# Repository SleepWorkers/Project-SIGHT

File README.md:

# Table of contents
- [Table of contents](#table-of-contents)
- [Introduction](#introduction)
- [About Project](#about-project)
- [Cloning project](#cloning-project)
  - [Users](#users)
  - [Developers](#developers)
    - [Ubuntu users](#ubuntu-users)
- [Folder information](#folder-information)
  - [Visible folders](#visible-folders)
  - [Hidden folders](#hidden-folders)

# Introduction
This repository is created for the purpose of participation in [IICDC 2018](https://innovate.mygov.in/india-innovation-challenge-design-contest-2018/) (India Innovation Challenge Design Contest). The project details _in short_ are summarized below:

|||
| ----- | ------ |
|**Project Name** | Project _SIGHT_ (Smart Infinity Glove using Heuristic Technology) - Transforming the way we live |
|**Submission ID** | 372888 |

# About Project
This project is created for the purpose of participation in [IICDC 2018](https://innovate.mygov.in/india-innovation-challenge-design-contest-2018/) (India Innovation Challenge Design Contest).

The human hand is the most versatile part of the body. We exploit its dexterity to provide a glove that can transcend today’s wearables by giving an organic feel while interacting with technology. We feeltoday,the most important and difficult to procure resources are time, money, health & safety. S.I.G.H.T. will safeguard these resources.

The project proposal file can be found [here](./.media/docs/372888_IICDC\ Proposal.pdf).

# Cloning project
## Users
To clone (download) the project, you can simply click on the **Clone or Download** button in the top right and download the entire project as a ZIP file.

## Developers
Before getting started, please go through the [contributing](./.github/CONTRIBUTING.md) guidelines.
You're suggested to clone this repository using the [git](https://git-scm.com/) tool which you can download [here](https://git-scm.com/downloads).
> **Tip**: Clone using [SSH](https://help.github.com/articles/connecting-to-github-with-ssh/) is a better idea.

### Ubuntu users
Open a terminal and do the following:
- _Install_ git
    ```bash
    sudo apt install git
    ```
- _cd_ into the directory where you want to clone
    ```bash
    cd ~
    ```
- _Clone_ the repository
  - Using SSH
    ```bash
    git clone git@github.com:SleepWorkers/Project-SIGHT.git
    ```
  - Using HTTPS
    ```bash
    git clone https://github.com/SleepWorkers/Project-SIGHT.git
    ```

# Folder information
Here are the folders available in this project

## Visible folders
<!-- TODO: Create a file structure and add description for it -->
|||
|-----|-----|
|**test** | Files used during the testing phase |
|**cad**  | CAD files (Electrical and mechanical) |
|**api**  | Final APIs of the product |
|**apps** | Final applications for the product |

## Hidden folders
|||
|-----|-----|
|**.github**| All GitHub related documents.|
|**.media**| Media files used for documentation purposes in the present working directory.|

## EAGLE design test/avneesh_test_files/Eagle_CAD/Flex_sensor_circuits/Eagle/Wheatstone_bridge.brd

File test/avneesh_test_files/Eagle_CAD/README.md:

# What is this?
This folder contains CAD files for [issue 15](https://github.com/SleepWorkers/Project-SIGHT/issues/15).

# Table of contents
- [What is this?](#what-is-this)
- [Table of contents](#table-of-contents)
- [Files and folders](#files-and-folders)
  - [Flex CV interface v1](#flex-cv-interface-v1)
  - [Flex connections](#flex-connections)
  - [Flex sensor circuits](#flex-sensor-circuits)

# Files and folders
## [Flex CV interface v1](./Flex_CV_interface_v1)
This folder contains files for the testing of the computer vision circuitry and the data collection algorithm part of [this issue](https://github.com/SleepWorkers/Project-SIGHT/issues/22). The files that are used for this are:

| **File Name** | **Purpose** |
| ---- | ---- |
| [*LED_connections.sch*](./Flex_CV_interface_v1/LED_connections.sch) | The LED connections to be made. Check Figure 1 (below) |

**Figure 1**: The LED connections to be made.

## [Flex connections](./Flex_connections/)
The flex sensor connections for the circuit. This is aligned with the API to generate the circuitry.

| **File Name** | **Purpose** |
| ---- | ---- |
| [Final_circuit.sch](./Flex_connections/Final_circuit.sch) | The final circuitry (template) |

## [Flex sensor circuits](./Flex_sensor_circuits/)
The individual flex sensor circuits for the connections. This is the final file having all the connection details.

[![TheProjectsGuy developer shield][TheProjectsGuy-dev-shield]][TheProjectsGuy-dev-profile]
[![Spawning Issue #22][issue-shield]][issue-link]

[TheProjectsGuy-dev-shield]: https://img.shields.io/badge/Dev-TheProjectsGuy-0061ff.svg
[TheProjectsGuy-dev-profile]: https://github.com/TheProjectsGuy
[issue-shield]: https://img.shields.io/badge/Issue-%2315-f49842.svg
[issue-link]: https://github.com/SleepWorkers/Project-SIGHT/issues/15

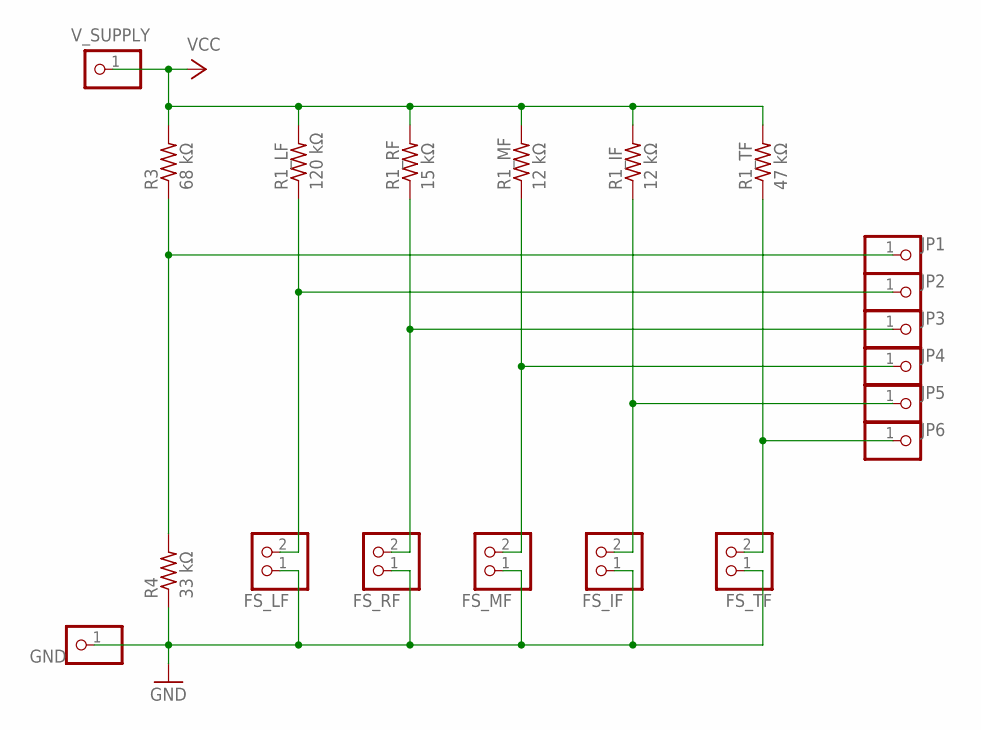
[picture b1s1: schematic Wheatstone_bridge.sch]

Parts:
FS_IF: PINHD-1X2; 1X02
FS_LF: PINHD-1X2; 1X02
FS_MF: PINHD-1X2; 1X02
FS_RF: PINHD-1X2; 1X02
FS_TF: PINHD-1X2; 1X02
GND: PINHD-1X1; 1X01
JP1, JP2, JP3, JP4, JP5, JP6: PINHD-1X1; 1X01
R1_IF, R1_MF: 12 kΩ; 0207/7
R1_LF: 120 kΩ; 0207/7
R1_RF: 15 kΩ; 0207/7
R1_TF: 47 kΩ; 0207/7
R3: 68 kΩ; 0207/7
R4: 33 kΩ; 0207/7
V_SUPPLY: PINHD-1X1; 1X01

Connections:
GND: FS_IF.1, FS_LF.1, FS_MF.1, FS_RF.1, FS_TF.1, GND.1, R4.1
unnamed: JP1.1, R3.1, R4.2
unnamed: FS_LF.2, JP2.1, R1_LF.1
unnamed: FS_TF.2, JP6.1, R1_TF.1
unnamed: FS_RF.2, JP3.1, R1_RF.1
unnamed: FS_MF.2, JP4.1, R1_MF.1
unnamed: FS_IF.2, JP5.1, R1_IF.1
VCC: R1_IF.2, R1_LF.2, R1_MF.2, R1_RF.2, R1_TF.2, R3.2, V_SUPPLY.1

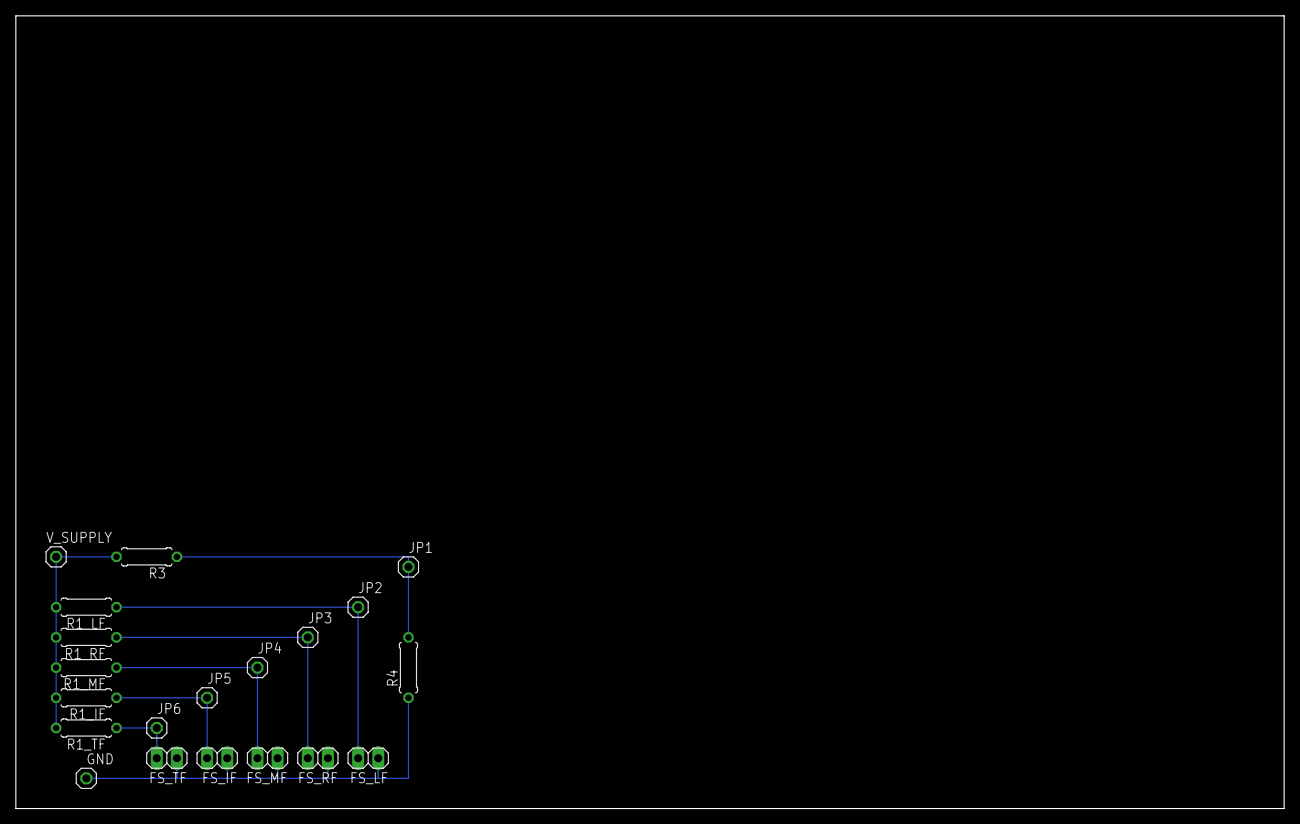
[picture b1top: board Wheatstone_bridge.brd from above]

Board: 2 copper layers, 160.0 x 100.0 mm, 20 parts (0 on the bottom side), 8 nets.

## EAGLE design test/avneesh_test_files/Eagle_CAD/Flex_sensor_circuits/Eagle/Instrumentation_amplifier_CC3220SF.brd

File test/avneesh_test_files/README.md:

# What is this?
This is the testing scratchpad of @TheProjectsGuy (Avneesh Mishra). All codes written here are just for testing purposes, once they're ready, they're moved into appropriate directories.

# Table of contents
- [What is this?](#what-is-this)
- [Table of contents](#table-of-contents)
- [Folders](#folders)

# Folders
Here's information about the folders present in this directory

| **Folder Name** | **Purpose** |
| ---- | ---- |
| [*cv_algo*](./cv_algo/) | All Computer vision related codes |
| [*TI_CC3220SF_WiFi_MCU*](./TI_CC3220SF_WiFi_MCU/) | All the codes related only to CC3220SF Launch XL |
| [*Eagle_CAD*](./Eagle_CAD/) | Eagle CAD files |
| [*Arduino_codes*](/Arduino_codes/) | Arduino test codes (just if you need an alternative) |
| [*MATLAB_scripts*](./MATLAB_scripts/) | MATLAB Script files used |
| [*APIs*](./APIs/) | The APIs created while testing |

[![TheProjectsGuy developer shield][TheProjectsGuy-dev-shield]][TheProjectsGuy-dev-profile]

[TheProjectsGuy-dev-shield]: https://img.shields.io/badge/Dev-TheProjectsGuy-0061ff.svg
[TheProjectsGuy-dev-profile]: https://github.com/TheProjectsGuy

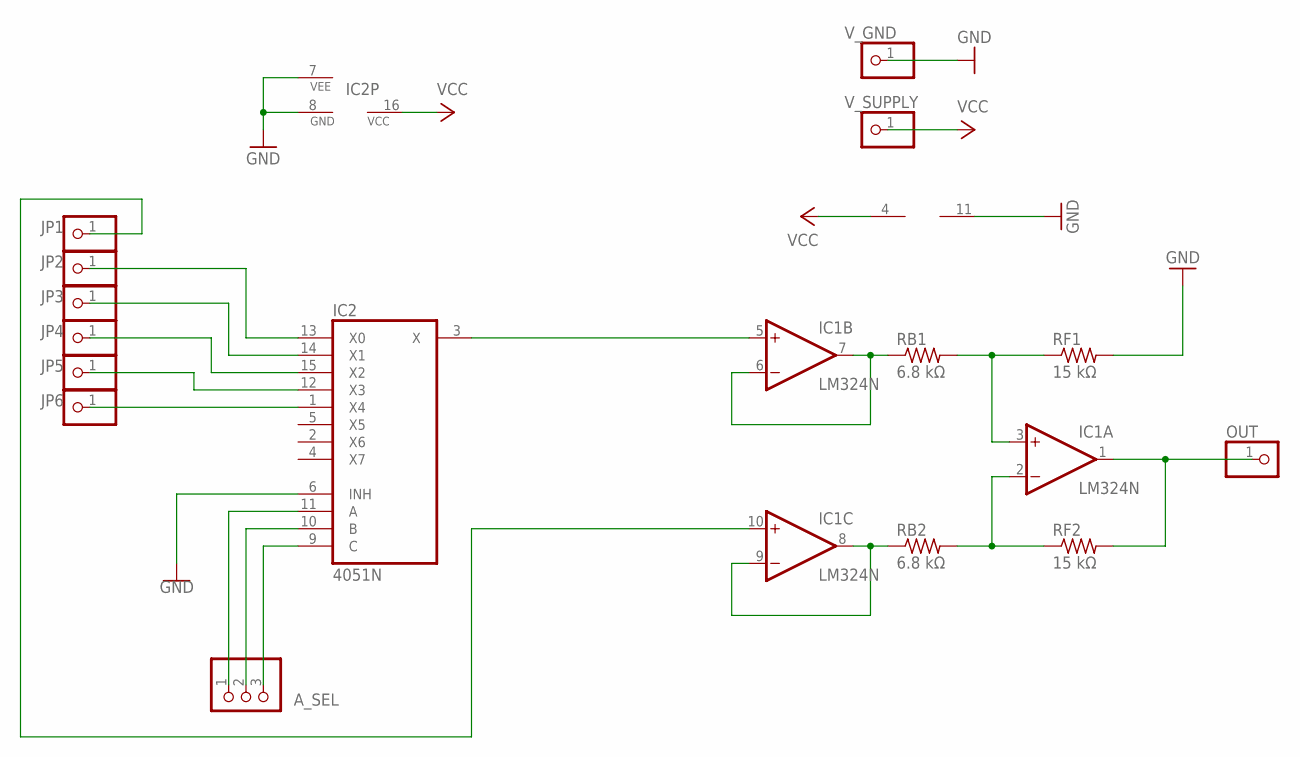
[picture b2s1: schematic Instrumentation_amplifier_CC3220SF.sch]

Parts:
A_SEL: PINHD-1X3; 1X03
IC1: LM324N; DIL14
IC2: 4051N; DIL16
JP1, JP2, JP3, JP4, JP5, JP6: PINHD-1X1; 1X01
OUT: PINHD-1X1; 1X01
RB1, RB2: 6.8 kΩ; 0204/7
RF1, RF2: 15 kΩ; 0204/7
V_GND: PINHD-1X1; 1X01
V_SUPPLY: PINHD-1X1; 1X01

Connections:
GND: IC1.11 (V-), IC2.6 (INH), IC2.7 (VEE), IC2.8 (GND), RF1.2, V_GND.1
unnamed: IC1.10 (+IN), JP1.1
unnamed: IC1.8 (OUT), IC1.9 (-IN), RB2.1
unnamed: IC1.2 (-IN), RB2.2, RF2.1
unnamed: IC1.6 (-IN), IC1.7 (OUT), RB1.1
unnamed: IC1.3 (+IN), RB1.2, RF1.1
unnamed: IC2.13 (X0), JP2.1
unnamed: IC1.5 (+IN), IC2.3 (X)
unnamed: IC2.14 (X1), JP3.1
unnamed: IC2.15 (X2), JP4.1
unnamed: IC1.1 (OUT), OUT.1, RF2.2
unnamed: IC2.12 (X3), JP5.1
unnamed: IC2.1 (X4), JP6.1
unnamed: A_SEL.1, IC2.11 (A)
unnamed: A_SEL.2, IC2.10 (B)
unnamed: A_SEL.3, IC2.9 (C)
VCC: IC1.4 (V+), IC2.16 (VCC), V_SUPPLY.1

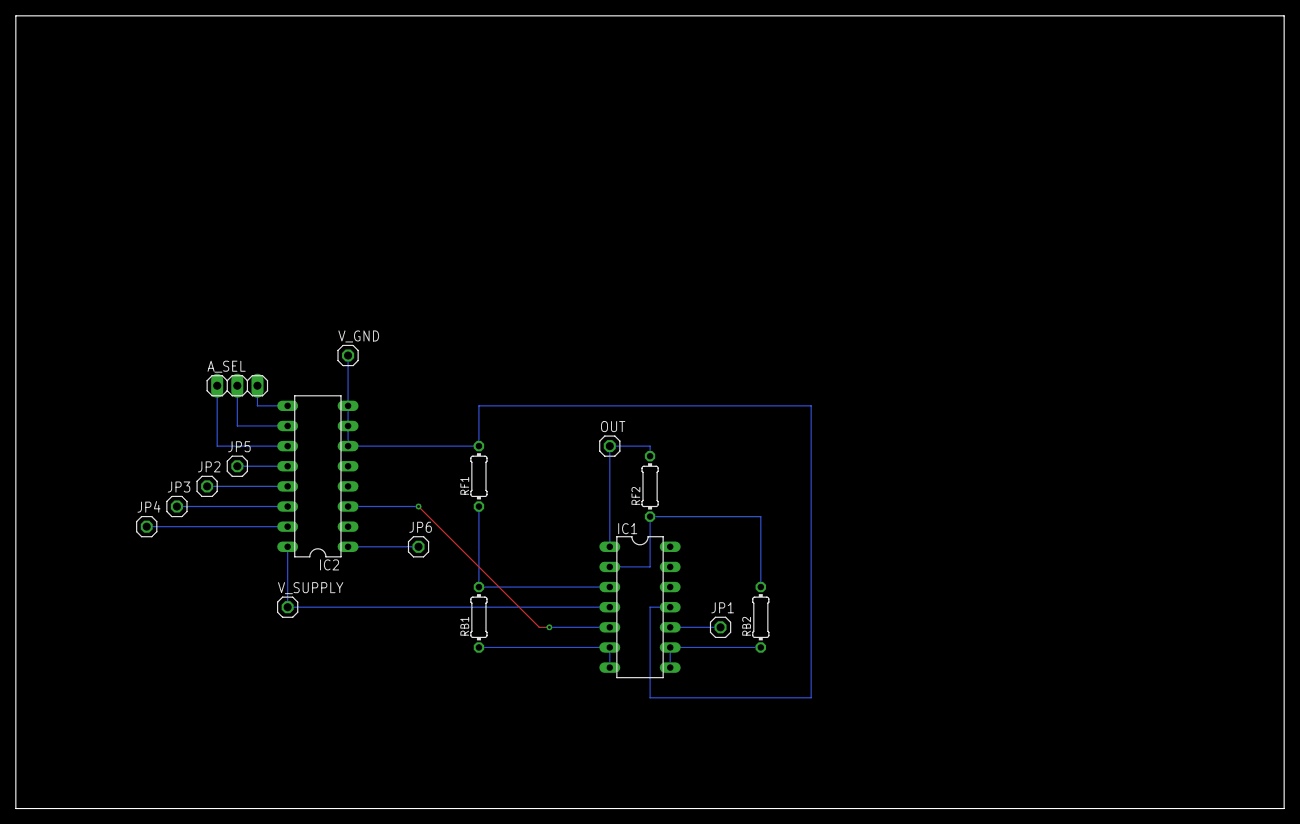
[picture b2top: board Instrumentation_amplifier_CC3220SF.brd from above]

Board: 2 copper layers, 160.0 x 100.0 mm, 16 parts (0 on the bottom side), 17 nets.

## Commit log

2019-01-03 Added README.md file
2019-01-03 Moved the Code of Conduct into .github folder
2019-01-03 Added a placeholder contributing file
2019-01-03 Added issue templates for documentation, feature requests and tasks
2019-01-03 Added pull request file
2019-01-03 Revert "Added pull request file"
2019-01-03 Reverted to an initial stage, trial
2019-01-03 Added fixes to the README file
2019-01-04 Added ISSUE TEMPLATE patches
2019-01-04 Added contribution guidelines
2019-01-04 README patches
2019-01-04 Added the project proposal file
2019-01-04 Added empty folders and files
2019-01-04 Added description on README.md
2019-01-04 Updated pull request template
2019-01-04 Modified photo
2019-01-04 Finished #5, issue completed
2019-01-04 Added references
    Added references for GitHub Desktop usage in the repository for Windows and MacOS
2019-01-04 Added README files for folders
    Empty README files created
2019-01-04 Updated GitHub Documents
    Made changes to pull request template, tasks template and contributing guidelines
2019-01-04 Updated README file
    Added MacOS and Windows clonig procedures and updated photo
2019-01-05 Added .gitignore file
2019-01-07 Added CONTRIBUTING and PulseSensor test codes
2019-01-07 Created branch for issue #12
2019-01-07 Added README ToC
2019-01-10 Created README for test directory
2019-01-10 Added analog flex sensor and serial interface
2019-01-17 Added developer shields and documentation work
2019-01-17 Pulse sensor arduino test [IGNORE]
2019-01-17 Modified README files with shields
2019-01-17 Started MATLAB tests
2019-01-17 Added README for issue #12
2019-01-17 Added documentation for issue #12
2019-01-17 Added text to files [IGNORE]
2019-01-17 Added OpAmp codes 1 and 2
2019-01-18 Added R2016a version
2019-01-18 Moved files into the versions folder
2019-01-18 Updated documentation (#12)
2019-01-26 Added milestone files
2019-01-26 Modified MATLAB files
2019-02-01 Added Instrumentation amplifier
2019-02-01 Added documentation
2019-02-01 Modified Simulink files [IGNORE]
2019-02-01 Created final simulation with the best results
2019-02-01 Added documentation for issue 16 and final MATLAB simulation
2019-02-01 Documentation patch for issue tracking
2019-02-01 Added folder description to README
2019-02-02 Create Pulse_Sensor_BPM.txt
    Code for getting BPM on Serial_Plotter
2019-02-05 Added modifications to resistance values, issue #16
2019-02-05 Added portability error message for MATLAB 2016b and below, issue #16 portability issue
2019-02-07 Renamed MATLAB_tests to MATLAB_tests_version1, issue #16
2019-02-07 Added MATLAB_tests_version2 folder, issue #16
2019-02-07 Updated license to Morzilla Public License
    The MIT License is too permissive. We need a little more restrictive and binding license.
2019-02-07 Added tests for version 2, final circuitry done. Progress on issue #16
2019-02-07 Added description files and pictures [Documentation], issue #16
2019-02-07 Added script file (resistance finder), issue #16
2019-02-08 Added more comments to Flex_sensor_debug.m file
2019-02-08 Added output text patch, issue #16
2019-02-08 Added documentation update
2019-02-08 SleepWorkers <-> Advanced Intelligent Robotics
2019-02-08 Added Eagle CAD files for version 1, issue #16
2019-02-15 Added files for second version Flex sensor debug
2019-02-15 Debug file changes
2019-02-15 Documentation update
2019-02-16 Added final script for issue #16
2019-02-16 Modified files to work with final script, issue #16
2019-02-16 Documentation update, issue #16
2019-02-16 Added CAD files for issue #16, solves and closes #16
2019-02-16 Documentation update for issue #16
2019-02-16 Patches added to MATLAB files
2019-02-17 Created empty file structure and avneesh-test-cv branch for issue #22
2019-02-19 Added .gitignore
2019-02-19 Added first README
2019-02-20 Added gitignore files
2019-02-20 [IGNORE] trial
2019-02-20 Added README.md
2019-02-20 #24 Arduino code for RPY
    Code Uses SparFun LSM9DS1 Library
2019-02-21 Fake image generator [INCOMPLETE], issue #22
2019-02-21 Added Digital output and Serial code "Blinks", issue #21
2019-02-21 [IGNORE] deleted the folder_sample folder
2019-02-21 Documentation for parts of issue #21
2019-02-21 [IGNORE] Removed .idea files
2019-02-21 Added empty directories for issue #22
2019-02-23 Added the gitignore file
2019-02-23 Tried out new values of resistors (hardware test failure), issue #22
2019-02-23 Added Arduino codes for issue #22
2019-02-23 Added Eagle CAD files for issue #22
2019-02-23 Added MATLAB scripts for issue #22
2019-02-23 Added cv_algo part for the issue #22
2019-02-23 Modified TI CC3220SF folder for future expansion
2019-02-23 Documentation update, issue #15
2019-02-24 Documentation patch done, solved issue #25
2019-02-24 Added MATLAB backup files in MATLAB_scripts, issue #21
2019-02-26 Not neccessary
2019-02-27 This is just a test commit testing Environment on Windows 10 for github: Will be working from Windows Not Ubuntu
2019-02-27 Test part 2 return to Original State
2019-03-03 Create CC2640R2F
2019-03-03 Add files via upload
    Added source documentation. Yet to include the sensor interfacing example code as I just got it installed after long, cumbersome process.
2019-03-03 Changed the Energia codes
2019-03-03 Added GPIO digital I/O and interrupts for issue #29
2019-03-04 Added PWM CCSv8 example codes for issue #29
2019-03-06 ADC example with Sensor Controller Studio & CCS
2019-03-06 Create ADC Example
2019-03-06 Create ADC
2019-03-06 Updated Readme for the Example
2019-03-06 Added example code for ADCs and UART along with documentation for issue #29
2019-03-07 Added changes to CV algorithm, issue #21
2019-03-07 Added TI CCS files for issue #21
2019-03-09 IGNORE
2019-03-09 Created file structure and branch for #31
2019-03-09 Changed code files for #31
2019-03-09 Added documentation for #31
2019-03-09 Generation API ready, issue #31 solved
2019-03-09 Added CAD files, closes issue #31
2019-03-10 Converted existing file to v1
2019-03-10 Updated documentation for #33
2019-03-11 Added serial side code for #33
2019-03-11 Added cv_bridge, issue #33 solved
2019-03-11 Added data_manip test files [IGNORE]
2019-03-12 Removed data files
2019-03-12 Added link to the CV bridge, issue #33
2019-03-13 Pulse Sensor ADC - HAL
2019-03-13 Pushing to API
2019-03-15 Added Flex sensor eagle files
2019-03-15 Added Eagle files for flex sensor
2019-03-16 Added code for I2C test
2019-03-16 Flex sensor circuitry update, issue #15
2019-03-16 [IGNORE] Documentation report
2019-03-17 Modification 1
2019-03-17 Added data
2019-03-17 Changed .mat file
2019-03-19 Updated flex sensor circuitry for new flex sensor
2019-03-19 Added Intrumentation amplifier CAD file
2019-03-19 Added changes to MATLAB files
2019-03-19 Board created for Wheatstone bridge side
2019-03-19 Added isntrumentation amplifier CAD files and board files
2019-03-20 Made changes to the CAD files
2019-03-20 Added gesture graph analyzer
2019-03-21 Create Serial_Communication
2019-03-21 Function
2019-03-21 Serial Communication
2019-03-21 Readme
2019-03-21 BPM calculator
2019-03-21 Uploaded Bluetooth Custom Profile files
2019-03-24 Added two more gestures
